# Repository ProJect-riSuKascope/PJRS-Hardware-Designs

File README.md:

# Project RisukaScope硬件系统
硬件系统主要分为以下几个部分：

## 电源
`/Power`文件夹。  
一个基于XL4016/SY8253的6~9V/5V/3.3V三轨供电系统。
此外还有一个给模拟前端用的5V模拟电源输出，用了一个LM1117-5.0。  
这部分十分臃肿，所以之后会做一个新的出来。

## 射频前端
`/RFFE`文件夹。  
前端LNA+滤波+多级Gain Block放大。  
前端LNA是NXP的BGU8009 GNSS LNA。  
滤波器是TA2494A。SAW滤波器，中心频率1420MHz，带宽80MHz。  
Gain Block用的是烂大街的SBB5089。  
Qucs仿真得到这个电路的增益~56dB，NF~0.66dB；实测增益48dB，NF因条件有限未测试。

## 调谐器与ADC
`Tuner ADC`文件夹。调谐器用的是各类SDR设备上常见的MSI001芯片，只用了L Band端口。实际试了一下应该有8MHz的带宽。  
ADC用的是AD9201，I/Q双通道同步采样ADC。  
系统采样率16MSPS。

## 通信与用户界面
`/Connectivity Interface`文件夹。
用了个ESP32-C3实现蓝牙/Wi-Fi通信。ESP32-C3通过SPI连接到FPGA。  
CD4504做缓冲器驱动舵机。  
预留了RGB LCD和以太网模块的接口。但目前还没用上。  
下面预留了八个机械键盘轴和两个电位器的位置，用于机械结构的操控。  
但后来想了想，感觉这样一点也不好用，不如直接遥控了。  
因为很多东西都没啥卵用，所以这部分也要大改。

## PMOD-Flash TinyRTC
`PMOD-Flash`文件夹。  
仿照Arduino平台上曾红极一时的I2C TinyRTC模块设计的PMOD Flash+RTC模块。  
一个W25N01 Flash+RX8010 RTC。RTC备份电源用的是硬币状的超级电容器。

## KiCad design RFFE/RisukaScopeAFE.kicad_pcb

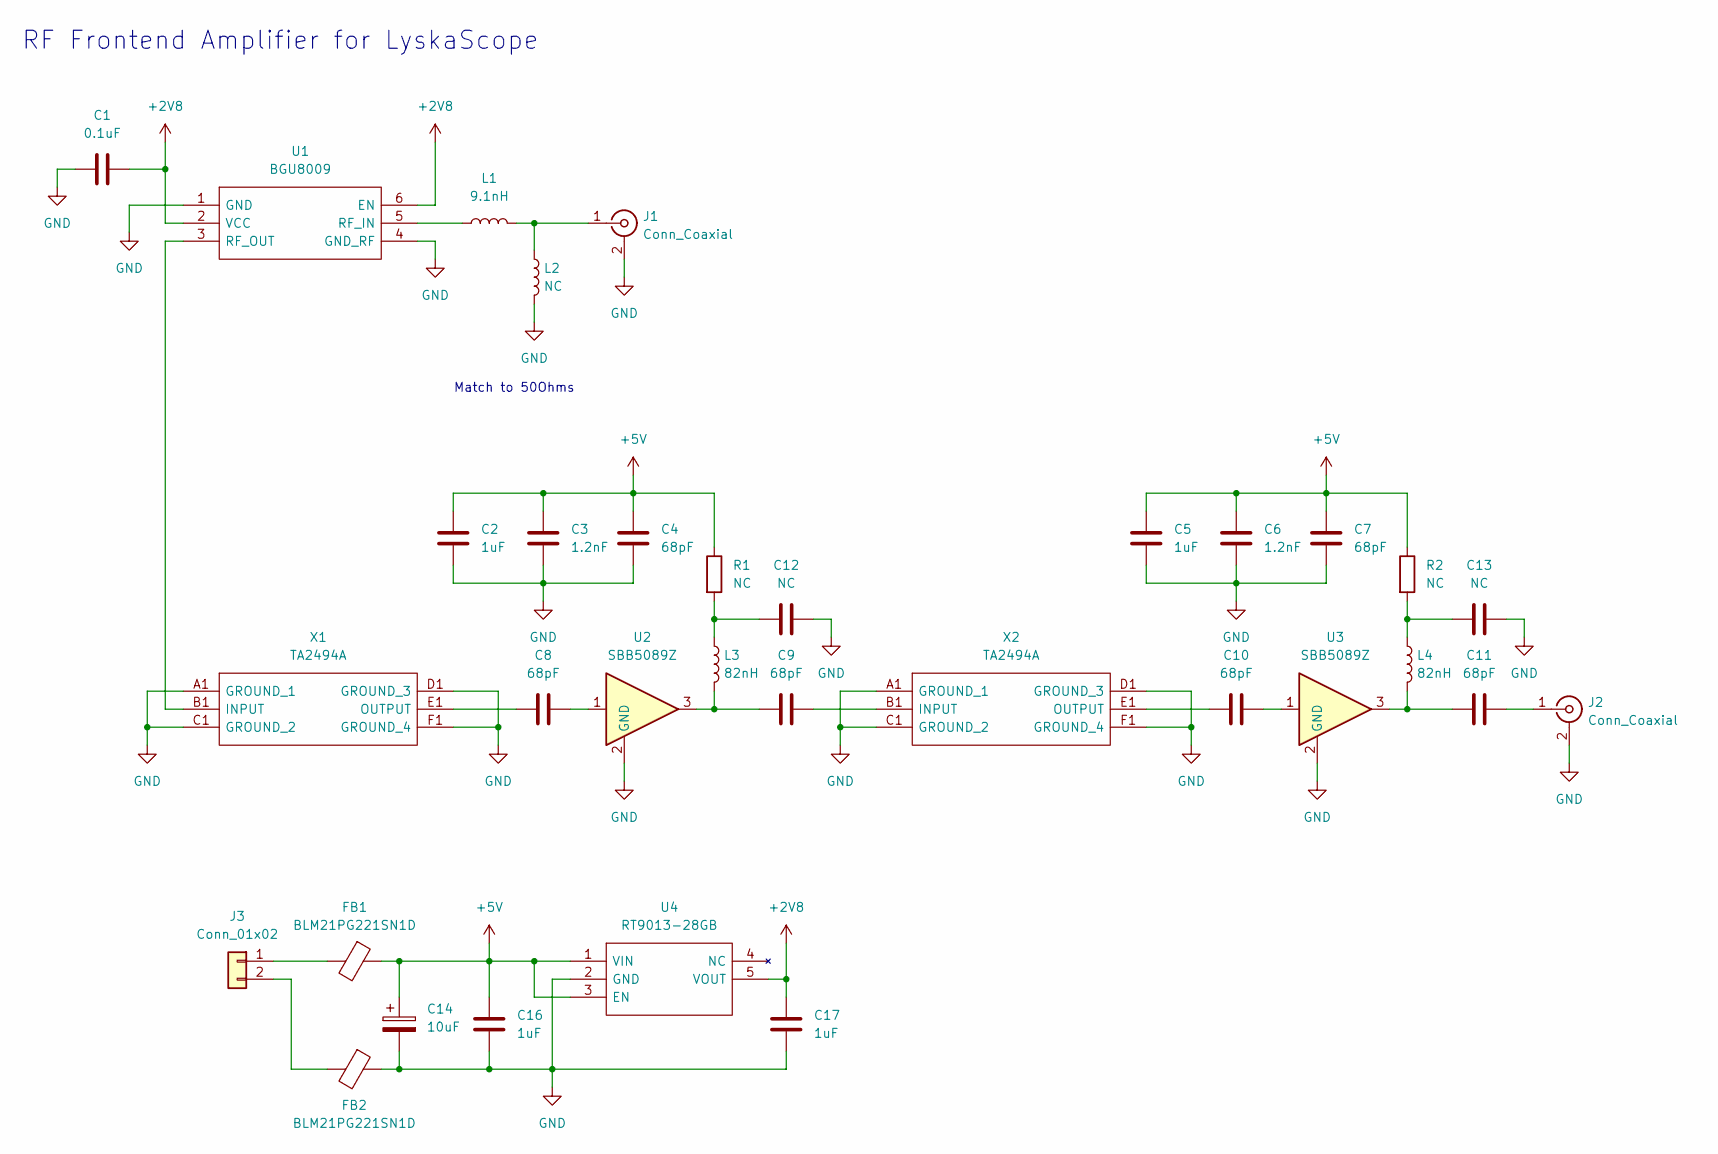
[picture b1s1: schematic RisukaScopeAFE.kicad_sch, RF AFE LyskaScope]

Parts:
C1: 0.1uF; C_0603_1608Metric
C2, C5, C16, C17: 1uF; C_0603_1608Metric
C3, C6: 1.2nF; C_0603_1608Metric
C4, C7, C8, C9, C10, C11: 68pF; C_0603_1608Metric
C12, C13: NC; C_0603_1608Metric
C14: 10uF; CP_EIA-3216-18_Kemet-A
FB1, FB2: BLM21PG221SN1D; L_0805_2012Metric
J1, J2: Conn_Coaxial; SMA_Samtec_SMA-J-P-X-ST-EM1_EdgeMount
J3: Conn_01x02; PinHeader_1x02_P2.54mm_Vertical
L1: 9.1nH; L_0603_1608Metric
L2: NC; L_0603_1608Metric
L3, L4: 82nH; L_0603_1608Metric
R1, R2: NC; R_0805_2012Metric
U1: BGU8009; SL3S1013FTB0115; Manufacturer_Part_Number BGU7005,115; Mouser Part Number 771-BGU7005115
U2, U3: SBB5089Z; SOT-89-3
U4: RT9013-28GB; SOT94P279X130-5N; Manufacturer_Part_Number RT9013-33GB
X1, X2: TA2494A; Manufacturer_Part_Number TA2494A

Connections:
+2V8: C1.1, C17.1, U1.2 (VCC), U1.6 (EN), U4.5 (VOUT)
+5V: C2.1, C3.1, C4.1, C5.1, C6.1, C7.1, C14.1, C16.1, FB1.1, R1.1, R2.1, U4.1 (VIN), U4.3 (EN)
GND: C1.2, C2.2, C3.2, C4.2, C5.2, C6.2, C7.2, C12.2, C13.2, C14.2, C16.2, C17.2, FB2.1, J1.2 (Ext), J2.2 (Ext), L2.2, U1.1 (GND), U1.4 (GND_RF), U2.2 (GND), U3.2 (GND), U4.2 (GND), X1.A1 (GROUND_1), X1.C1 (GROUND_2), X1.D1 (GROUND_3), X1.F1 (GROUND_4), X2.A1 (GROUND_1), X2.C1 (GROUND_2), X2.D1 (GROUND_3), X2.F1 (GROUND_4)
unnamed: C8.1, U2.1
unnamed: C8.2, X1.E1 (OUTPUT)
unnamed: C9.1, X2.B1 (INPUT)
unnamed: C9.2, L3.2, U2.3
unnamed: C10.1, U3.1
unnamed: C10.2, X2.E1 (OUTPUT)
unnamed: C11.1, J2.1 (In)
unnamed: C11.2, L4.2, U3.3
unnamed: FB1.2, J3.1
unnamed: FB2.2, J3.2
unnamed: J1.1 (In), L1.2, L2.1
unnamed: L1.1, U1.5 (RF_IN)
unnamed: C12.1, L3.1, R1.2
unnamed: C13.1, L4.1, R2.2
unnamed: U1.3 (RF_OUT), X1.B1 (INPUT)

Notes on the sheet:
Match to 50Ohms
RF Frontend Amplifier for LyskaScope

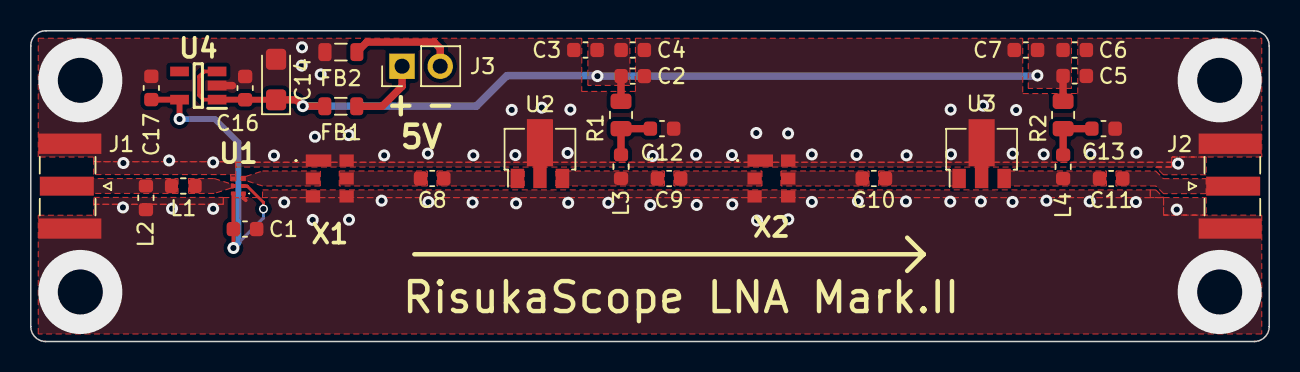
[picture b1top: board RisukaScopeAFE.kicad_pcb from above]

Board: 2 copper layers, 82.5 x 20.7 mm, 33 parts (0 on the bottom side), 18 nets.

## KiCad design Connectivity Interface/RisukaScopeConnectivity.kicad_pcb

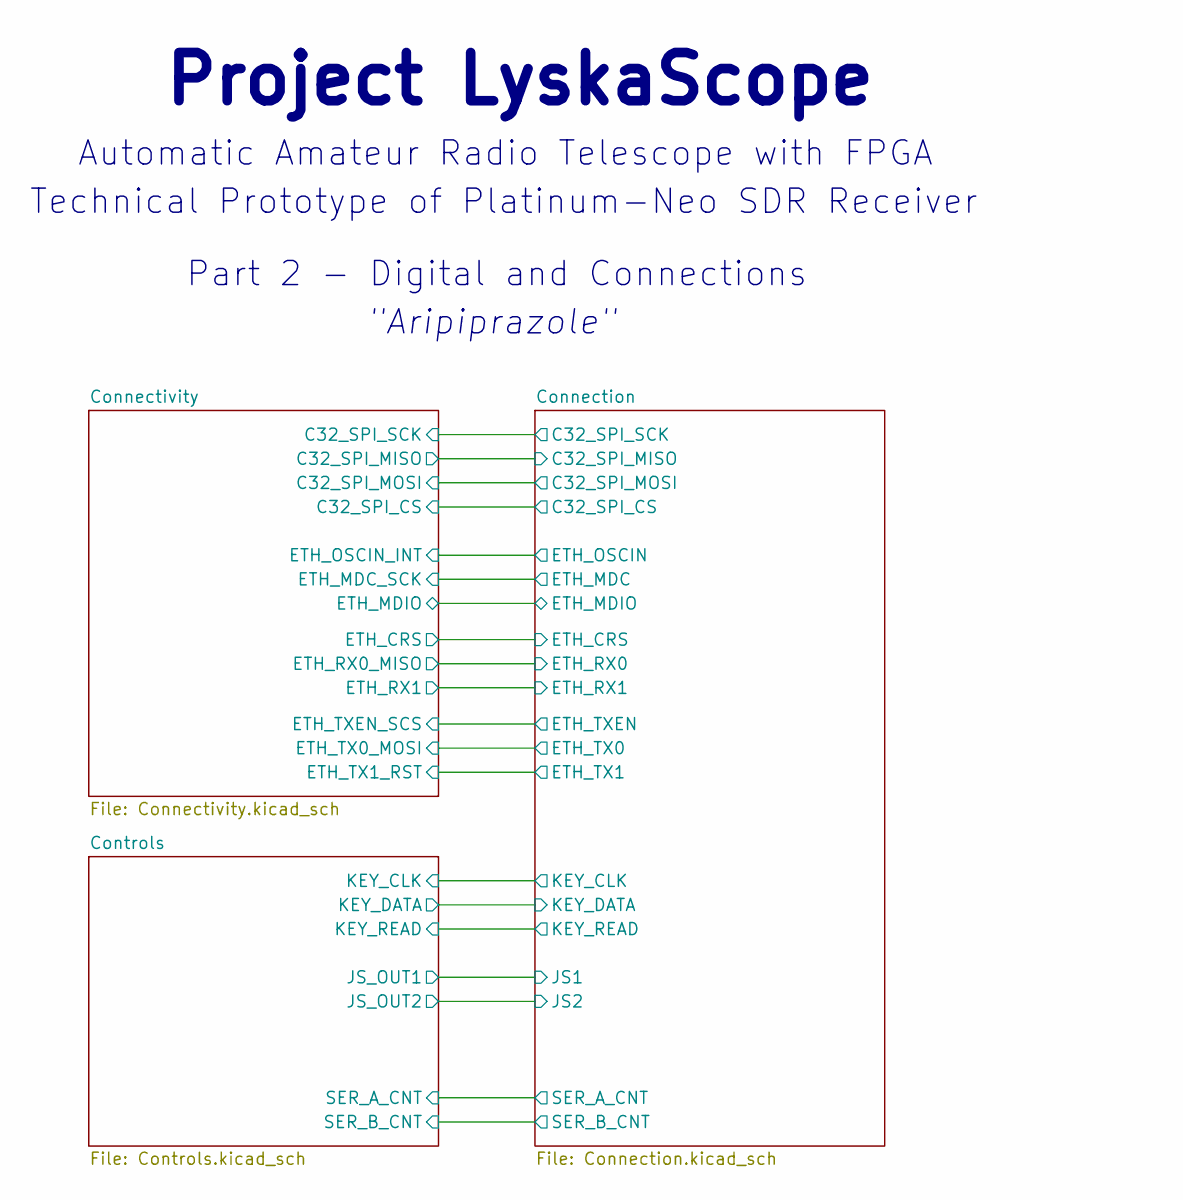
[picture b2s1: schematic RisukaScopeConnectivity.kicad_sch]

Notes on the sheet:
Project LyskaScope
Technical Prototype of Platinum-Neo SDR Receiver
"Aripiprazole"
Part 2 - Digital and Connections
Automatic Amateur Radio Telescope with FPGA

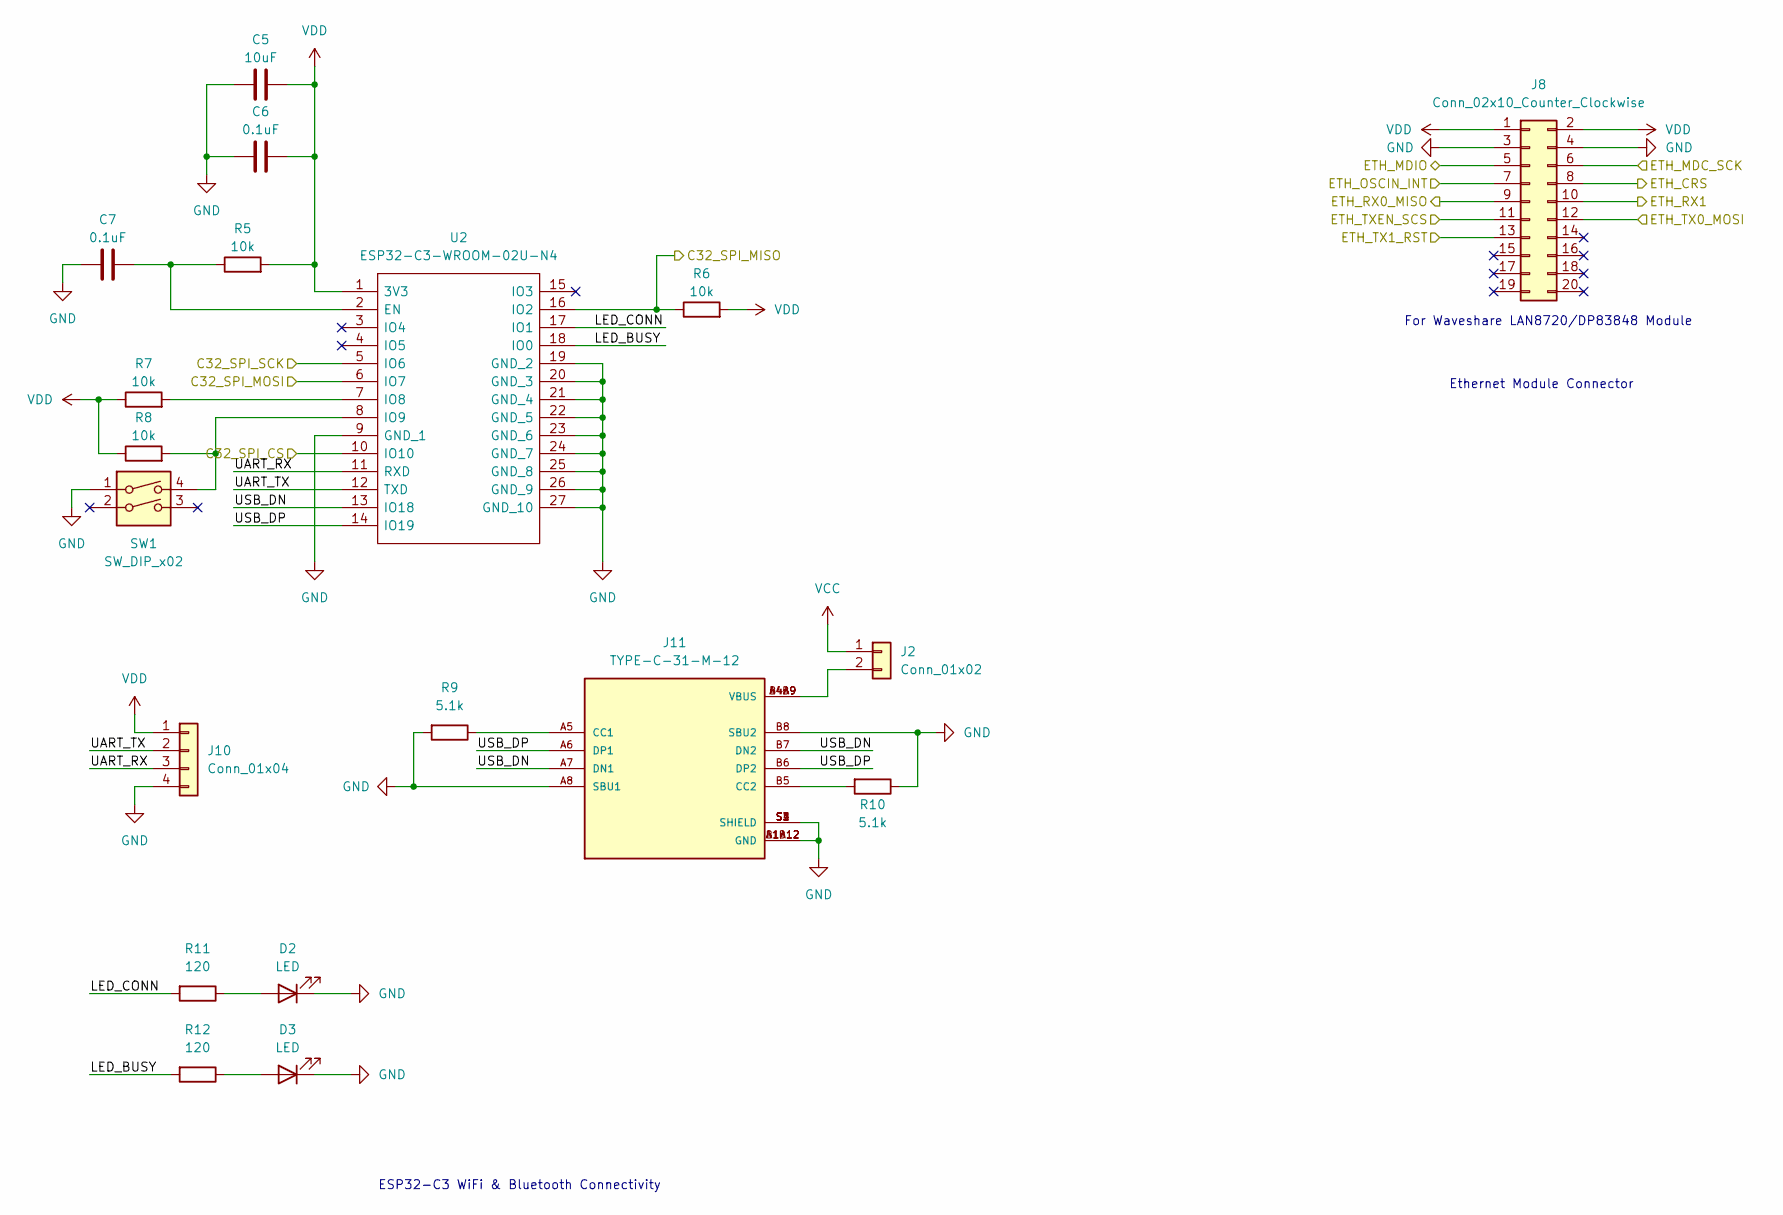
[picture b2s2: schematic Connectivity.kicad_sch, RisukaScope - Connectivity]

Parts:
C5: 10uF; C_0603_1608Metric
C6, C7: 0.1uF; C_0603_1608Metric
D2, D3: LED; LED_0603_1608Metric
J2: Conn_01x02; PinHeader_1x02_P2.54mm_Vertical
J8: Conn_02x10_Counter_Clockwise; PinHeader_2x10_P2.54mm_Vertical
J10: Conn_01x04; PinHeader_1x04_P2.54mm_Vertical
J11: TYPE-C-31-M-12; HRO_TYPE-C-31-M-12; PARTREV A
R5, R6, R7, R8: 10k; R_0603_1608Metric
R9, R10: 5.1k; R_0603_1608Metric
R11, R12: 120; R_0603_1608Metric
SW1: SW_DIP_x02; DSHP02TSGET
U2: ESP32-C3-WROOM-02U-N4; ESP32C3WROOM02UN4; Manufacturer_Part_Number ESP32-C3-WROOM-02U-N4; Mouser Part Number 356-ESP32C3WROM02UN4

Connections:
/Connection/C32_SPI_CS: U2.10 (IO10); also elsewhere on the board
/Connection/C32_SPI_MISO: R6.1, U2.16 (IO2); also elsewhere on the board
/Connection/C32_SPI_MOSI: U2.6 (IO7); also elsewhere on the board
/Connection/C32_SPI_SCK: U2.5 (IO6); also elsewhere on the board
/Connection/ETH_CRS: J8.8; also elsewhere on the board
/Connection/ETH_MDC: J8.6; also elsewhere on the board
/Connection/ETH_MDIO: J8.5; also elsewhere on the board
/Connection/ETH_OSCIN: J8.7; also elsewhere on the board
/Connection/ETH_RX0: J8.9; also elsewhere on the board
/Connection/ETH_RX1: J8.10; also elsewhere on the board
/Connection/ETH_TX0: J8.12; also elsewhere on the board
/Connection/ETH_TX1: J8.13; also elsewhere on the board
/Connection/ETH_TXEN: J8.11; also elsewhere on the board
/Connectivity/LED_BUSY: R12.2, U2.18 (IO0)
/Connectivity/LED_CONN: R11.2, U2.17 (IO1)
/Connectivity/UART_RX: J10.3, U2.11 (RXD)
/Connectivity/UART_TX: J10.2, U2.12 (TXD)
/Connectivity/USB_DN: J11.A7 (DN1), J11.B7 (DN2), U2.13 (IO18)
/Connectivity/USB_DP: J11.A6 (DP1), J11.B6 (DP2), U2.14 (IO19)
GND: C5.2, C6.2, C7.2, D2.1 (K), D3.1 (K), J8.3, J8.4, J10.4, J11.A1B12 (GND), J11.A8 (SBU1), J11.B1A12 (GND), J11.B8 (SBU2), J11.S1 (SHIELD), J11.S2 (SHIELD), J11.S3 (SHIELD), J11.S4 (SHIELD), R9.2, R10.1, SW1.1, U2.9 (GND_1), U2.19 (GND_2), U2.20 (GND_3), U2.21 (GND_4), U2.22 (GND_5), U2.23 (GND_6), U2.24 (GND_7), U2.25 (GND_8), U2.26 (GND_9), U2.27 (GND_10); also elsewhere on the board
unnamed: C7.1, R5.1, U2.2 (EN)
unnamed: D2.2 (A), R11.1
unnamed: D3.2 (A), R12.1
unnamed: J2.2, J11.A4B9 (VBUS), J11.B4A9 (VBUS)
unnamed: J11.A5 (CC1), R9.1
unnamed: J11.B5 (CC2), R10.2
unnamed: R7.2, U2.7 (IO8)
unnamed: R8.2, SW1.4, U2.8 (IO9)
VCC: J2.1; also elsewhere on the board
VDD: C5.1, C6.1, J8.1, J8.2, J10.1, R5.2, R6.2, R7.1, R8.1, U2.1 (3V3); also elsewhere on the board

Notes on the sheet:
Ethernet Module Connector
ESP32-C3 WiFi & Bluetooth Connectivity
For Waveshare LAN8720/DP83848 Module

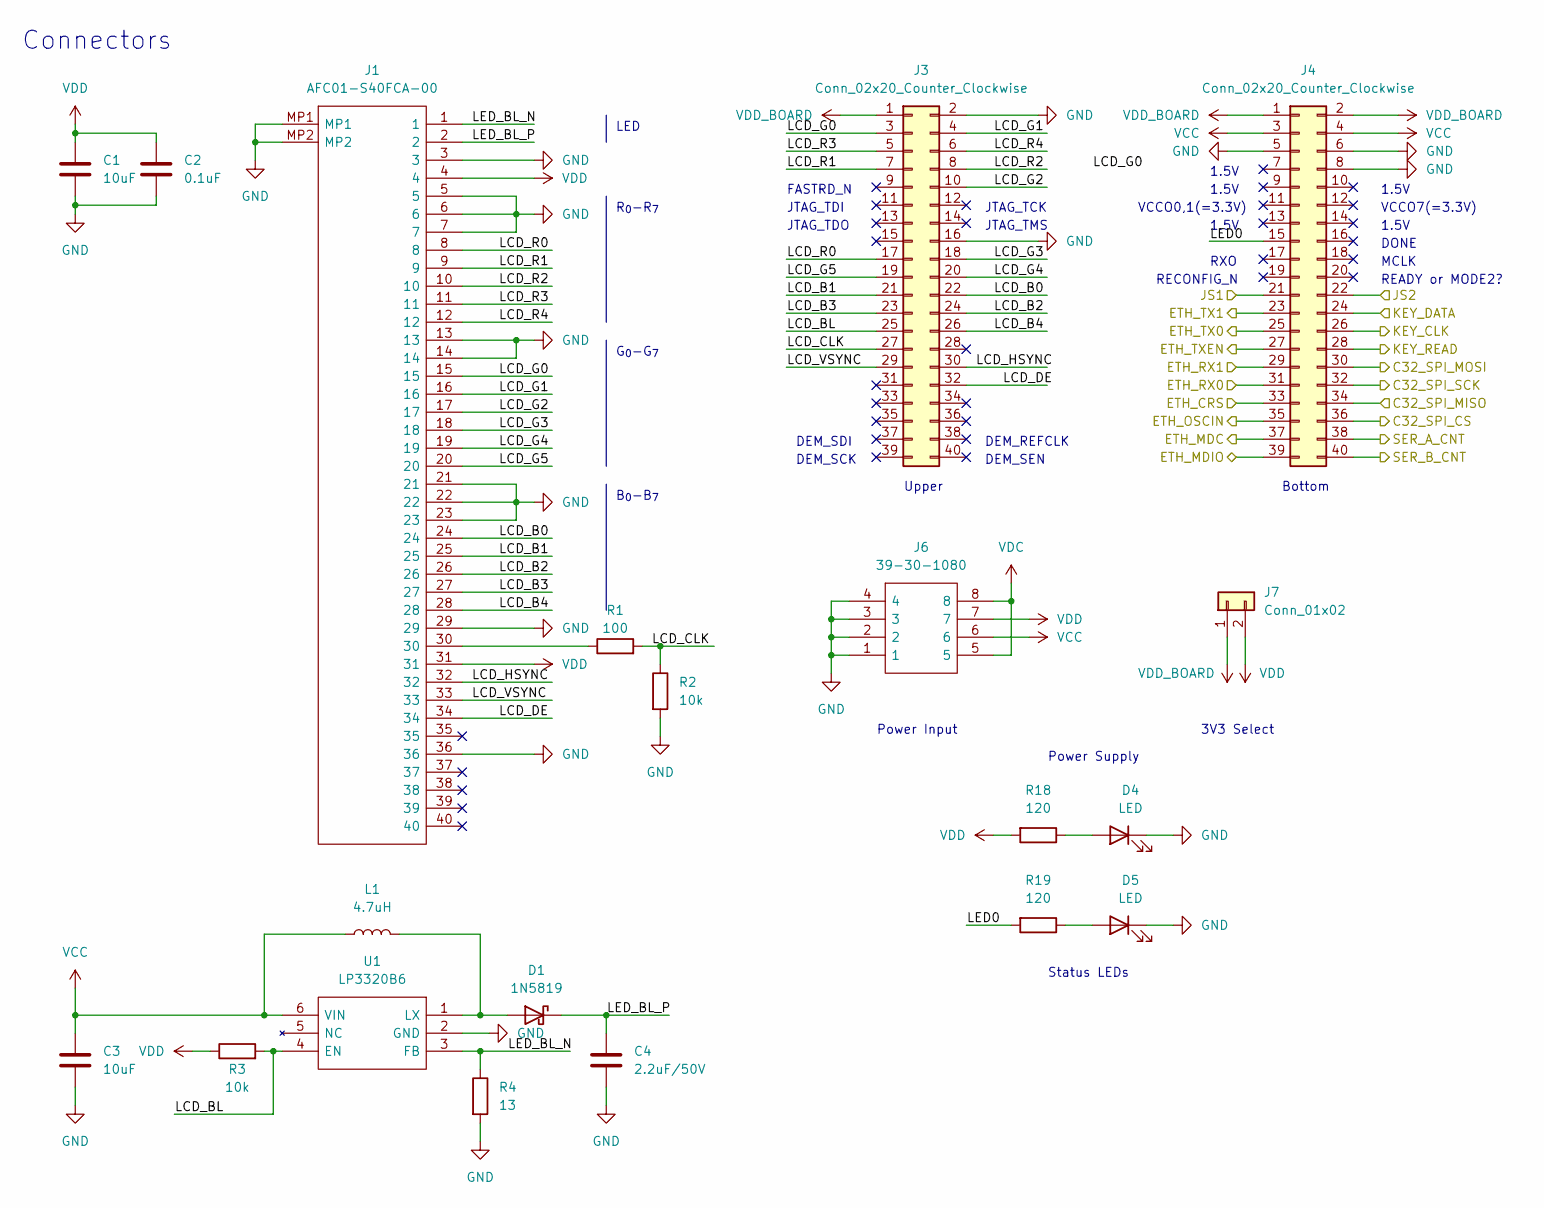
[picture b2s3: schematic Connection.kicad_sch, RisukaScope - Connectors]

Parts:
C1, C3: 10uF; C_0603_1608Metric
C2: 0.1uF; C_0603_1608Metric
C4: 2.2uF/50V; C_0805_2012Metric
D1: 1N5819; D_SOD-323
D4, D5: LED; LED_0603_1608Metric
J1: AFC01-S40FCA-00; AFC01S40FCA00; Manufacturer_Part_Number AFC01-S40FCA-00
J3, J4: Conn_02x20_Counter_Clockwise; PinHeader_2x20_P2.54mm_Vertical
J6: 39-30-1080; 39-30-Y080; Manufacturer_Part_Number 39-30-1080; Mouser Part Number 538-39-30-1080
J7: Conn_01x02; PinHeader_1x02_P2.54mm_Vertical
L1: 4.7uH; INDPM3030X150N
R1: 100; R_0603_1608Metric
R2, R3: 10k; R_0603_1608Metric
R4: 13; R_0603_1608Metric
R18, R19: 120; R_0603_1608Metric
U1: LP3320B6; SOT94P279X130-6N; Manufacturer_Part_Number LP3320B6

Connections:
/Connection/C32_SPI_CS: J4.36; also elsewhere on the board
/Connection/C32_SPI_MISO: J4.34; also elsewhere on the board
/Connection/C32_SPI_MOSI: J4.30; also elsewhere on the board
/Connection/C32_SPI_SCK: J4.32; also elsewhere on the board
/Connection/ETH_CRS: J4.33; also elsewhere on the board
/Connection/ETH_MDC: J4.37; also elsewhere on the board
/Connection/ETH_MDIO: J4.39; also elsewhere on the board
/Connection/ETH_OSCIN: J4.35; also elsewhere on the board
/Connection/ETH_RX0: J4.31; also elsewhere on the board
/Connection/ETH_RX1: J4.29; also elsewhere on the board
/Connection/ETH_TX0: J4.25; also elsewhere on the board
/Connection/ETH_TX1: J4.23; also elsewhere on the board
/Connection/ETH_TXEN: J4.27; also elsewhere on the board
/Connection/JS1: J4.21; also elsewhere on the board
/Connection/JS2: J4.22; also elsewhere on the board
/Connection/KEY_CLK: J4.26; also elsewhere on the board
/Connection/KEY_DATA: J4.24; also elsewhere on the board
/Connection/KEY_READ: J4.28; also elsewhere on the board
/Connection/LCD_B0: J1.24, J3.22
/Connection/LCD_B1: J1.25, J3.21
/Connection/LCD_B2: J1.26, J3.24
/Connection/LCD_B3: J1.27, J3.23
/Connection/LCD_B4: J1.28, J3.26
/Connection/LCD_BL: J3.25, R3.2, U1.4 (EN)
/Connection/LCD_CLK: J3.27, R1.2, R2.1
/Connection/LCD_DE: J1.34, J3.32
/Connection/LCD_G0: J1.15, J3.3
/Connection/LCD_G1: J1.16, J3.4
/Connection/LCD_G2: J1.17, J3.10
/Connection/LCD_G3: J1.18, J3.18
/Connection/LCD_G4: J1.19, J3.20
/Connection/LCD_G5: J1.20, J3.19
/Connection/LCD_HSYNC: J1.32, J3.30
/Connection/LCD_R0: J1.8, J3.17
/Connection/LCD_R1: J1.9, J3.7
/Connection/LCD_R2: J1.10, J3.8
/Connection/LCD_R3: J1.11, J3.5
/Connection/LCD_R4: J1.12, J3.6
/Connection/LCD_VSYNC: J1.33, J3.29
/Connection/LED0: J4.15, R19.2
/Connection/LED_BL_N: J1.1, R4.1, U1.3 (FB)
/Connection/LED_BL_P: C4.1, D1.1 (K), J1.2
/Connection/SER_A_CNT: J4.38; also elsewhere on the board
/Connection/SER_B_CNT: J4.40; also elsewhere on the board
GND: C1.2, C2.2, C3.2, C4.2, D4.1 (K), D5.1 (K), J1.3, J1.5, J1.6, J1.7, J1.13, J1.14, J1.21, J1.22, J1.23, J1.29, J1.36, J1.MP1, J1.MP2, J3.2, J3.16, J4.5, J4.6, J4.8, J6.1, J6.2, J6.3, J6.4, R2.2, R4.2, U1.2 (GND); also elsewhere on the board
unnamed: D1.2 (A), L1.2, U1.1 (LX)
unnamed: D4.2 (A), R18.1
unnamed: D5.2 (A), R19.1
unnamed: J1.30, R1.1
VCC: C3.1, J4.3, J4.4, J6.6, L1.1, U1.6 (VIN); also elsewhere on the board
VDC: J6.5, J6.8; also elsewhere on the board
VDD: C1.1, C2.1, J1.4, J1.31, J6.7, J7.2, R3.1, R18.2; also elsewhere on the board
VDD_BOARD: J3.1, J4.1, J4.2, J7.1

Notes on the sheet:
1.5V
RECONFIG_N
R_{0}-R_{7}
Upper
DEM_SDI
DEM_SEN
JTAG_TDI
3V3 Select
MCLK
RXO
DONE
VCCO7(=3.3V)
JTAG_TCK
JTAG_TMS
JTAG_TDO
LED
Connectors
Bottom
DEM_REFCLK
DEM_SCK
READY or MODE2?
FASTRD_N
Power Input
G_{0}-G_{7}
VCCO0,1(=3.3V)
Status LEDs
B_{0}-B_{7}
Power Supply

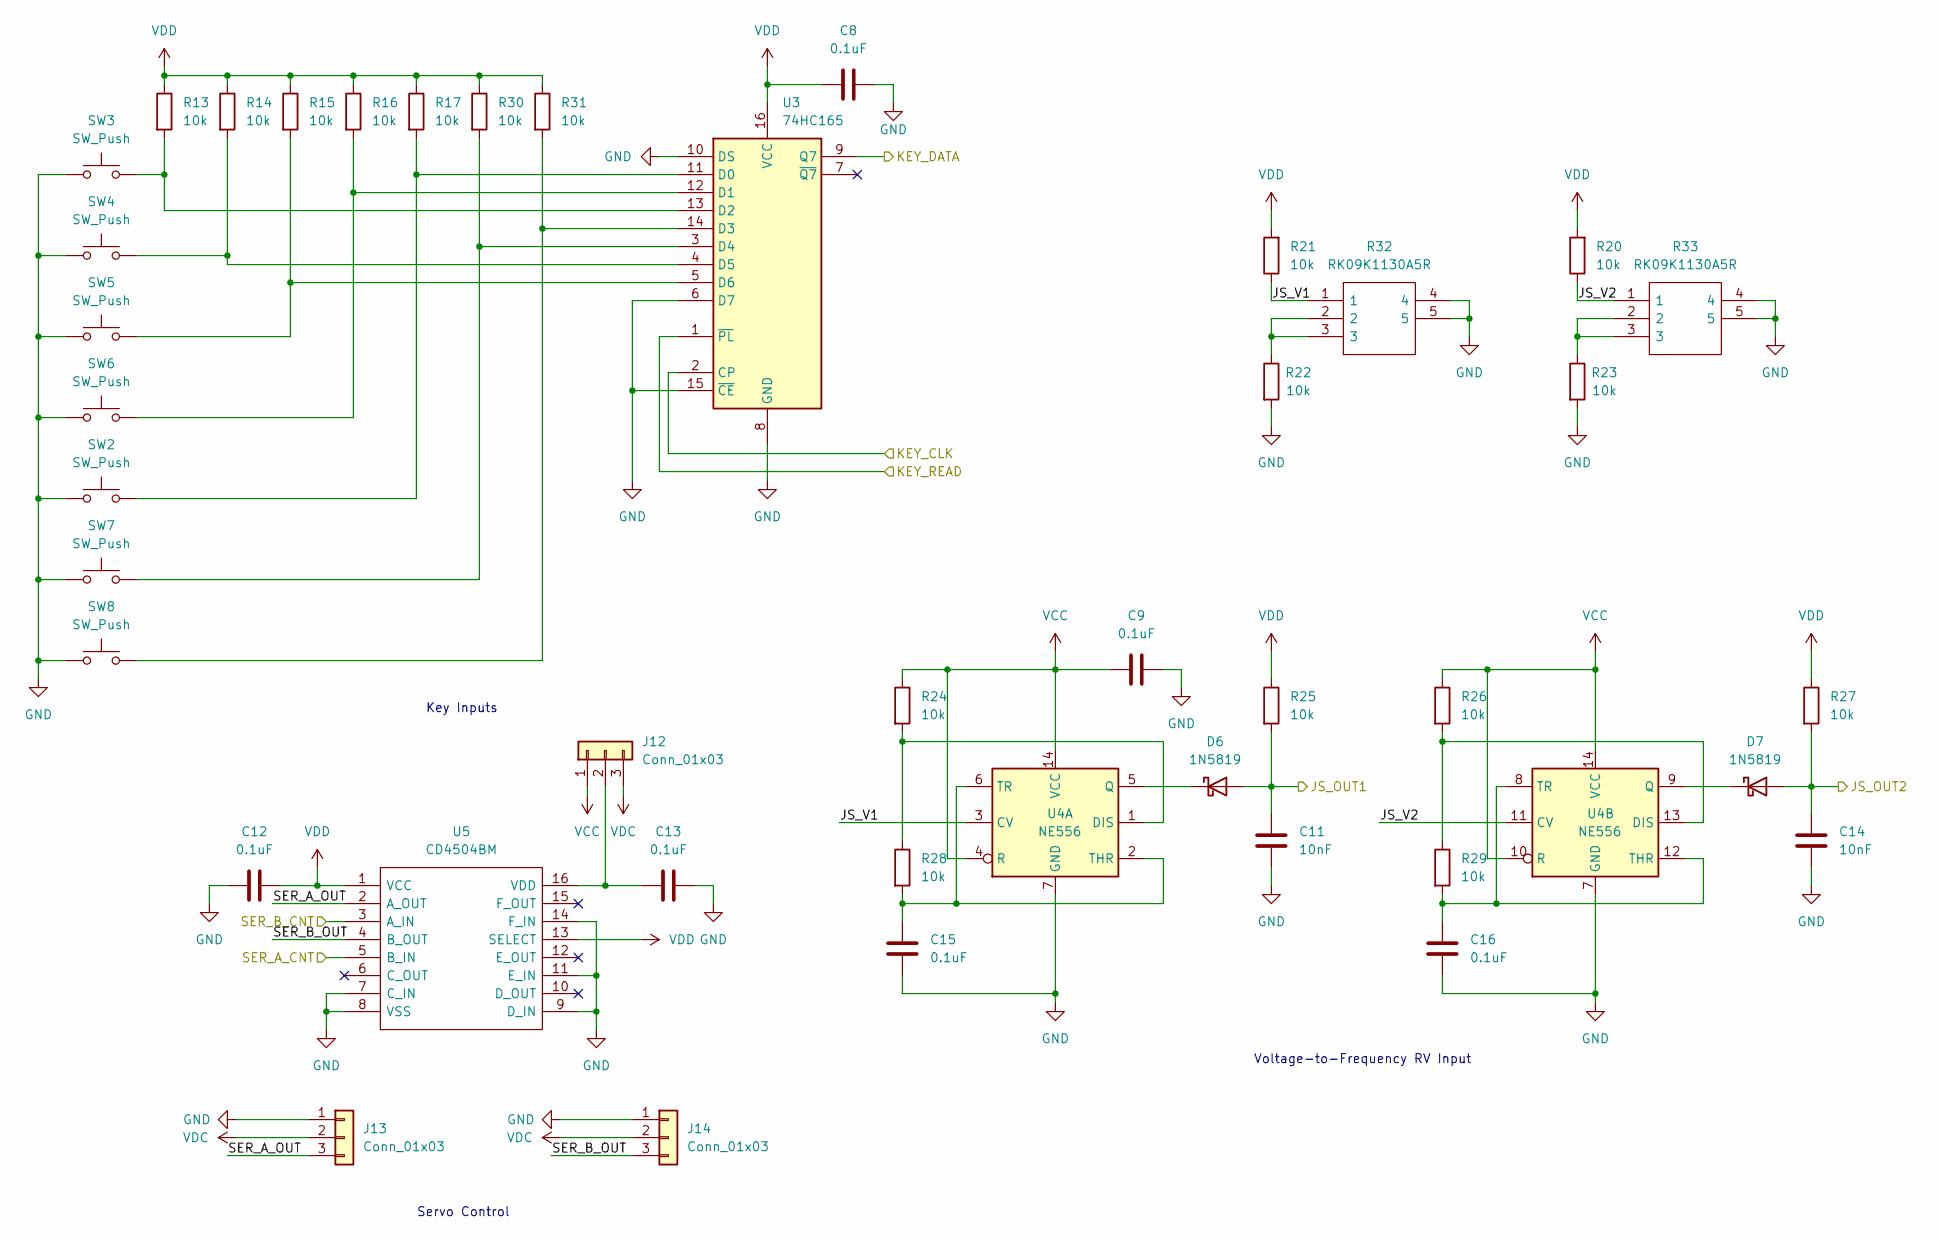
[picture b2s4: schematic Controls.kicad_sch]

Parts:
C8, C9, C12, C13, C15, C16: 0.1uF; C_0603_1608Metric
C11, C14: 10nF; C_0603_1608Metric
D6, D7: 1N5819; D_SOD-323
J12, J13, J14: Conn_01x03; PinHeader_1x03_P2.54mm_Vertical
R13, R14, R15, R16, R17, R20, R21, R22, R23, R24, R25, R26, R27, R28, R29, R30, R31: 10k; R_0603_1608Metric
R32, R33: RK09K1130A5R; Manufacturer_Part_Number RK09K1130A5R; Mouser Part Number 688-RK09K1130A5R
SW2, SW3, SW4, SW5, SW6: SW_Push; CPG135001D03
SW7, SW8: SW_Push; CPG135001D03_1U5
U3: 74HC165; SOP-16_3.9x9.9mm_P1.27mm
U4: NE556; SOIC-14_3.9x8.7mm_P1.27mm
U5: CD4504BM; SOIC127P600X175-16N; Manufacturer_Part_Number CD4504BM; Mouser Part Number 595-CD4504BM

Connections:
/Connection/JS1: C11.1, D6.2 (A), R25.2; also elsewhere on the board
/Connection/JS2: C14.1, D7.2 (A), R27.2; also elsewhere on the board
/Connection/KEY_CLK: U3.2 (CP); also elsewhere on the board
/Connection/KEY_DATA: U3.9 (Q7); also elsewhere on the board
/Connection/KEY_READ: U3.1 (~PL); also elsewhere on the board
/Connection/SER_A_CNT: U5.5 (B_IN); also elsewhere on the board
/Connection/SER_B_CNT: U5.3 (A_IN); also elsewhere on the board
/Controls/JS_V1: R21.1, R32.1, U4.3 (CV)
/Controls/JS_V2: R20.1, R33.1, U4.11 (CV)
/Controls/SER_A_OUT: J13.3, U5.2 (A_OUT)
/Controls/SER_B_OUT: J14.3, U5.4 (B_OUT)
GND: C8.2, C9.2, C11.2, C12.2, C13.1, C14.2, C15.2, C16.2, J13.1, J14.1, R22.2, R23.2, R32.4, R32.5, R33.4, R33.5, SW2.1, SW3.1, SW4.1, SW5.1, SW6.1, SW7.1, SW8.1, U3.6 (D7), U3.8 (GND), U3.10 (DS), U3.15 (~CE), U4.7 (GND), U5.7 (C_IN), U5.8 (VSS), U5.9 (D_IN), U5.11 (E_IN), U5.14 (F_IN); also elsewhere on the board
unnamed: C13.2, J12.2, U5.16 (VDD)
unnamed: C15.1, R28.2, U4.2 (THR), U4.6 (TR)
unnamed: C16.1, R29.2, U4.8 (TR), U4.12 (THR)
unnamed: D6.1 (K), U4.5 (Q)
unnamed: D7.1 (K), U4.9 (Q)
unnamed: R13.2, SW3.2, U3.13 (D2)
unnamed: R14.2, SW4.2, U3.4 (D5)
unnamed: R15.2, SW5.2, U3.5 (D6)
unnamed: R16.2, SW6.2, U3.12 (D1)
unnamed: R17.2, SW2.2, U3.11 (D0)
unnamed: R22.1, R32.2, R32.3
unnamed: R23.1, R33.2, R33.3
unnamed: R24.2, R28.1, U4.1 (DIS)
unnamed: R26.2, R29.1, U4.13 (DIS)
unnamed: R30.2, SW7.2, U3.3 (D4)
unnamed: R31.2, SW8.2, U3.14 (D3)
VCC: C9.1, J12.1, R24.1, R26.1, U4.4 (R), U4.10 (R), U4.14 (VCC); also elsewhere on the board
VDC: J12.3, J13.2, J14.2; also elsewhere on the board
VDD: C8.1, C12.1, R13.1, R14.1, R15.1, R16.1, R17.1, R20.2, R21.2, R25.1, R27.1, R30.1, R31.1, U3.16 (VCC), U5.1 (VCC), U5.13 (SELECT); also elsewhere on the board

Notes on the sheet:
Servo Control
Key Inputs
Voltage-to-Frequency RV Input

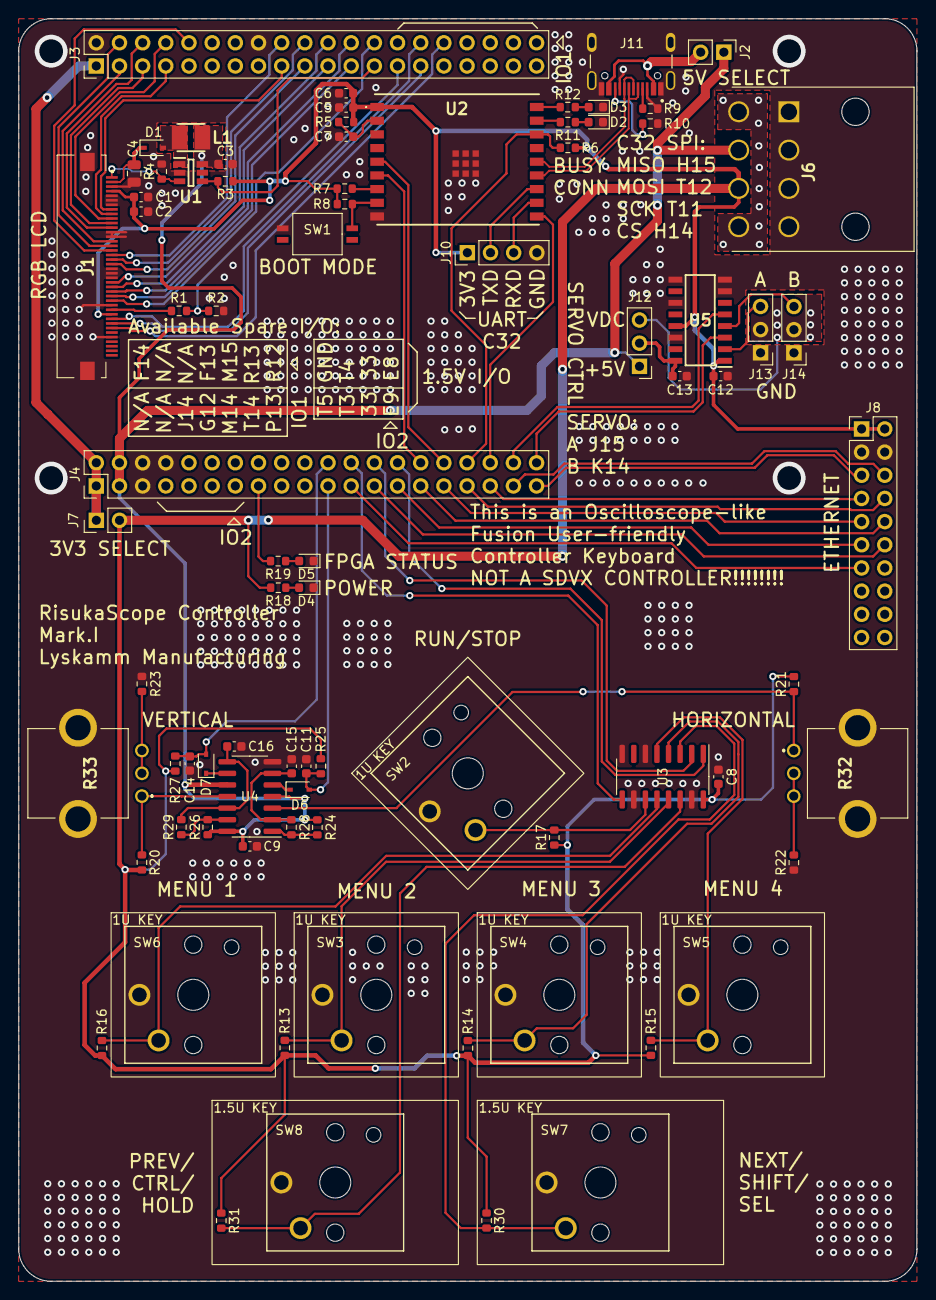
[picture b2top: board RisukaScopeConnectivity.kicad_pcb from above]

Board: 2 copper layers, 98.5 x 138.4 mm, 81 parts (0 on the bottom side), 87 nets.

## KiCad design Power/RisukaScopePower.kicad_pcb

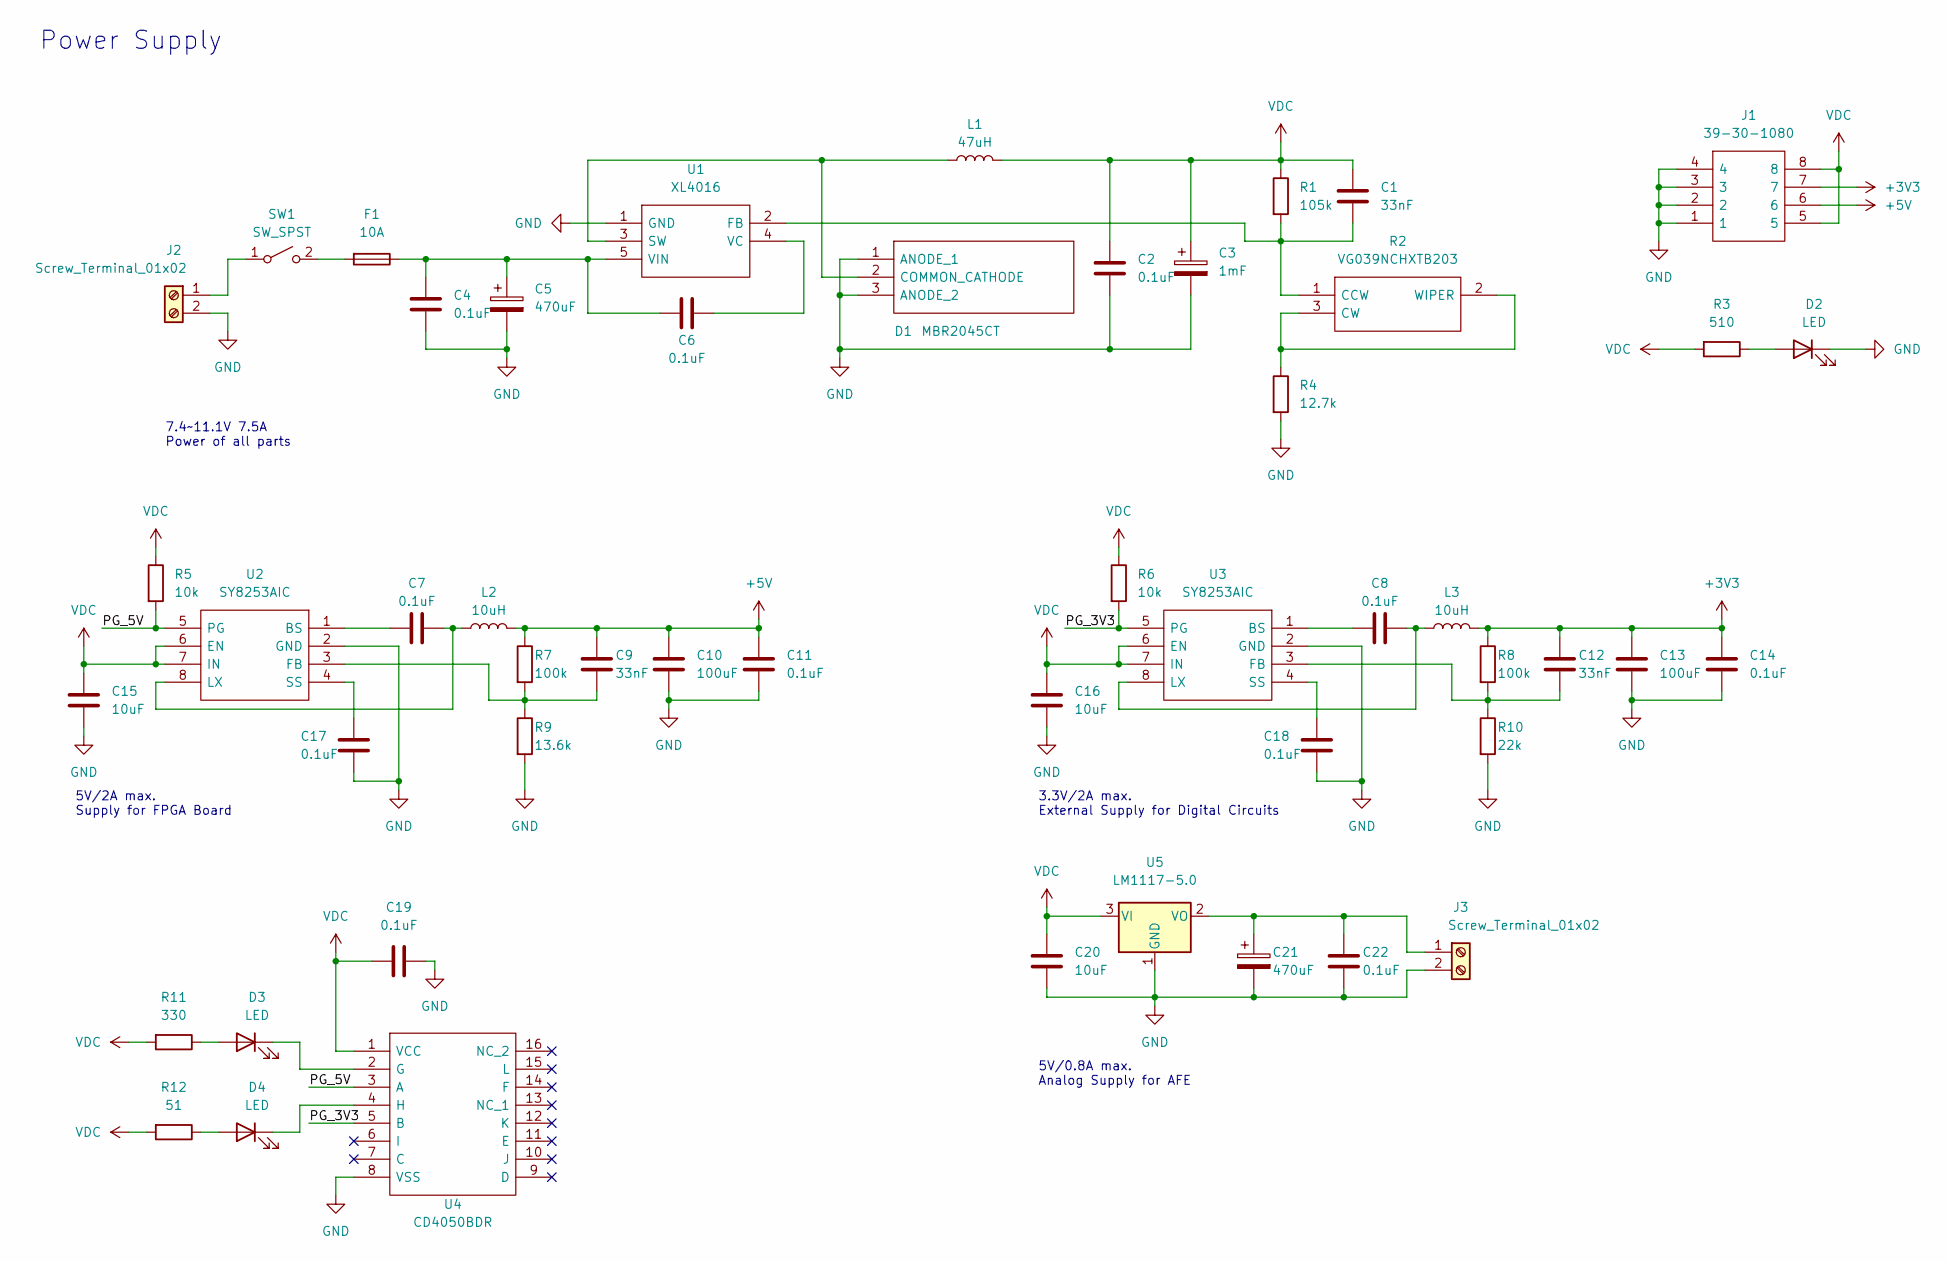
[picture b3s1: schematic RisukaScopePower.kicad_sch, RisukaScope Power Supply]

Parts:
C1, C9, C12: 33nF; C_0603_1608Metric
C2, C4, C6, C7, C8, C11, C14, C17, C18, C19, C22: 0.1uF; C_0603_1608Metric
C3: 1mF; CP_Radial_D10.0mm_P5.00mm
C5, C21: 470uF; CP_Elec_10x10.5
C10, C13: 100uF; C_1206_3216Metric
C15, C16, C20: 10uF; C_0603_1608Metric
D1: MBR2045CT; TO254P450X1000X2010-3P; Manufacturer_Part_Number MBR2045CT; Mouser Part Number 621-MBR2045CT
D2, D3, D4: LED; LED_0603_1608Metric
F1: 10A; 64600001003
J1: 39-30-1080; 39-30-Y080; Manufacturer_Part_Number 39-30-1080; Mouser Part Number 538-39-30-1080
J2, J3: Screw_Terminal_01x02; TerminalBlock_MetzConnect_Type101_RT01602HBWC_1x02_P5.08mm_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
L1: 47uH; L_Toroid_Vertical_L21.6mm_W9.5mm_P7.11mm_Pulse_C
L2, L3: 10uH; INDPM5452X300N
R1: 105k; R_0603_1608Metric
R2: VG039NCHXTB203; Manufacturer_Part_Number VG039NCHXTB203
R3: 510; R_0805_2012Metric
R4: 12.7k; R_0603_1608Metric
R5, R6: 10k; R_0603_1608Metric
R7, R8: 100k; R_0603_1608Metric
R9: 13.6k; R_0603_1608Metric
R10: 22k; R_0603_1608Metric
R11: 330; R_0805_2012Metric
R12: 51; R_0805_2012Metric
SW1: SW_SPST; SS11-BBIWQ-R20-R
U1: XL4016; Manufacturer_Part_Number XL4016
U2, U3: SY8253AIC; SOT65P280X110-8N; Manufacturer_Part_Number SY8253AIC
U4: CD4050BDR; SOIC127P600X175-16N; Manufacturer_Part_Number CD4050BDR; Mouser Part Number 595-CD4050BDR
U5: LM1117-5.0; TO-220-3_Vertical

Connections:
+3V3: C12.1, C13.1, C14.1, J1.7, L3.2, R8.1
+5V: C9.1, C10.1, C11.1, J1.6, L2.2, R7.1
/PG_3V3: R6.2, U3.5 (PG), U4.5 (B)
/PG_5V: R5.2, U2.5 (PG), U4.3 (A)
GND: C2.2, C3.2, C4.2, C5.2, C10.2, C11.2, C13.2, C14.2, C15.2, C16.2, C17.2, C18.2, C19.2, C20.2, C21.2, C22.2, D1.1 (ANODE_1), D1.3 (ANODE_2), D2.1 (K), J1.1, J1.2, J1.3, J1.4, J2.2, J3.2, R4.2, R9.2, R10.2, U1.1 (GND), U2.2 (GND), U3.2 (GND), U4.8 (VSS), U5.1 (GND)
unnamed: C1.2, R1.2, R2.1 (CCW), U1.2 (FB)
unnamed: C4.1, C5.1, C6.2, F1.1, U1.5 (VIN)
unnamed: C6.1, U1.4 (VC)
unnamed: C7.1, U2.1 (BS)
unnamed: C7.2, L2.1, U2.8 (LX)
unnamed: C8.1, U3.1 (BS)
unnamed: C8.2, L3.1, U3.8 (LX)
unnamed: C9.2, R7.2, R9.1, U2.3 (FB)
unnamed: C12.2, R8.2, R10.1, U3.3 (FB)
unnamed: C17.1, U2.4 (SS)
unnamed: C18.1, U3.4 (SS)
unnamed: C21.1, C22.1, J3.1, U5.2 (VO)
unnamed: D1.2 (COMMON_CATHODE), L1.1, U1.3 (SW)
unnamed: D2.2 (A), R3.1
unnamed: D3.1 (K), U4.2 (G)
unnamed: D3.2 (A), R11.1
unnamed: D4.1 (K), U4.4 (H)
unnamed: D4.2 (A), R12.1
unnamed: F1.2, SW1.2 (B)
unnamed: J2.1, SW1.1 (A)
unnamed: R2.2 (WIPER), R2.3 (CW), R4.1
VDC: C1.1, C2.1, C3.1, C15.1, C16.1, C19.1, C20.1, J1.5, J1.8, L1.2, R1.1, R3.2, R5.1, R6.1, R11.2, R12.2, U2.6 (EN), U2.7 (IN), U3.6 (EN), U3.7 (IN), U4.1 (VCC), U5.3 (VI)

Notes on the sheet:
7.4~11.1V 7.5A Power of all parts
Power Supply
5V/0.8A max. Analog Supply for AFE
5V/2A max. Supply for FPGA Board
3.3V/2A max. External Supply for Digital Circuits
